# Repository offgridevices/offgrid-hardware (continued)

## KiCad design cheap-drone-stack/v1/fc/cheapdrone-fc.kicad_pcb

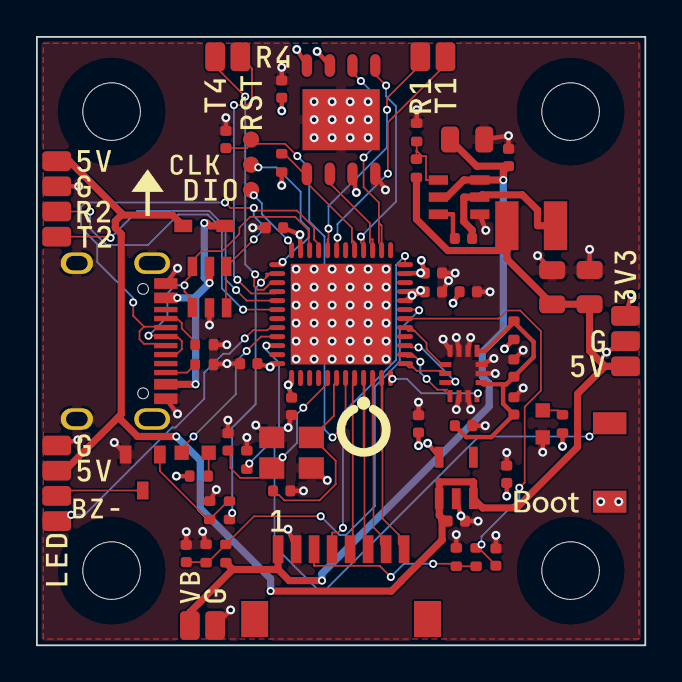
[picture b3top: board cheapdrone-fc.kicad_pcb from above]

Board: 4 copper layers, 33.8 x 33.8 mm, 77 parts (0 on the bottom side), 49 nets.

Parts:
C1, C2, C4, C5, C10, C11, C12, C13, C14, C17, C21, C22, C23: 100nF; C_0402_1005Metric
C3: 10uF; C_0805_2012Metric
C6, C7: 22uF; C_0805_2012Metric
C8, C15: 1uF; C_0402_1005Metric
C9, C16, C20: 4.7uF; C_0402_1005Metric
C18, C19: 12pF; C_0402_1005Metric
D_USB: 1N5819WS; SOD-323_L1.8-W1.3-LS2.5-RD
H1, H2, H3, H4: HOLE; HOLE_M3
J_ESC: SH-8P RA; CONN-TH_SM08B-SRSS-TB-LF-SN
J_USB: USB-C; USB-C_SMD-TYPE-C-31-M-12_1
L1: 4.7uH; IND-SMD_L3.0-W3.0_FNR30XXS
LED_PWR: RED; LED-SMD_L1.6-W0.8-R-RD
LED_STAT: BLUE; LED0603-RD_BLUE
P_3V3, P_5V: PAD_SIG
P_BZ+: PAD_SIG
P_BZ-: PAD_SIG
P_G1, P_G2, P_G3: PAD_SIG
P_LED: PAD_SIG
P_R1, P_R2, P_R4: PAD_SIG
P_RX5V: PAD_SIG
P_RXG: PAD_SIG
P_T1, P_T2, P_T4: PAD_SIG
P_VBAT: PAD_SIG
Q_BZ: 2N7002; SOT-23-3_L2.9-W1.3-P1.90-LS2.4-BR
R1: 100k; R_0402_1005Metric
R2, R4, R12, R13: 1k; R_0402_1005Metric
R3, R7, R9, R15: 10k; R_0402_1005Metric
R5: 15k; R_0402_1005Metric
R6: 2k; R_0402_1005Metric
R8: 10R; R_0402_1005Metric
R10, R11: 5.1k; R_0402_1005Metric
R14: 100R; R_0402_1005Metric
SW_BOOT: BOOT; SW-SMD_L3.9-W3.0-P4.45
TP_NRST: PAD_TP
TP_SWCLK: PAD_TP
TP_SWDIO: PAD_TP
U_BUCK: LMR51420YDDCR; SOT-23-6_L2.9-W1.6-P0.95-LS2.9-BL
U_ESD: USBLC6-2SC6; SOT-23-6_L2.9-W1.6-P0.95-LS2.8-BL
U_FC: STM32G473CEU6; UFQFPN-48_L7.0-W7.0-P0.50-BL-EP5.6
U_FLASH: W25Q128JVPIQ; WSON-8_L6.0-W5.0-P1.27-BL-EP
U_IMU: ICM-42688-P; LGA-14_L3.0-W2.5-P0.50-TL
U_LDO: ME6211C33; SOT-23-5_L3.0-W1.7-P0.95-LS2.8-BL
Y1: 8MHz; CRYSTAL-SMD_4P-L3.2-W2.5-BL

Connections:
+3V3: C9.1, C10.1, C11.1, C12.1, C13.1, C14.1, C15.1, C16.1, C23.1, P_3V3.1, R8.1, R9.1, R12.1, R13.1, SW_BOOT.1, U_FC.1, U_FC.20, U_FC.21, U_FC.23, U_FC.35, U_FC.48, U_FLASH.3, U_FLASH.7, U_FLASH.8, U_LDO.5
+3V3_GYRO: C20.1, C21.1, C22.1, R8.2, U_IMU.5, U_IMU.8
+5V: C6.1, C7.1, C8.1, D_USB.1, L1.2, P_5V.1, P_BZ+.1, P_RX5V.1, R5.1, U_LDO.1, U_LDO.3
ADC_CURR: C1.1, R2.2, U_FC.18
ADC_VBAT: C2.1, R3.2, R4.1, U_FC.19
BEEPER: R14.1, U_FC.38
BEEPER_G: Q_BZ.1, R14.2, R15.1
BOOT0: R7.1, SW_BOOT.2, U_FC.46
BUCK_CB: C5.1, U_BUCK.6
BUCK_FB: R5.2, R6.1, U_BUCK.4
BUCK_SW: C5.2, L1.1, U_BUCK.2
BZ-: P_BZ-.1, Q_BZ.3
CUR: J_ESC.3, R1.1, R2.1
FLASH_CS: R9.2, U_FC.29, U_FLASH.1
GND: C1.2, C2.2, C3.2, C4.2, C6.2, C7.2, C8.2, C9.2, C10.2, C11.2, C12.2, C13.2, C14.2, C15.2, C16.2, C17.2, C18.2, C19.2, C20.2, C21.2, C22.2, C23.2, J_ESC.2, J_USB.1, J_USB.2, J_USB.3, J_USB.4, J_USB.A1B12, J_USB.B1A12, LED_PWR.2, P_G1.1, P_G2.1, P_G3.1, P_RXG.1, Q_BZ.2, R1.2, R4.2, R6.2, R7.2, R10.2, R11.2, R15.2, U_BUCK.1, U_ESD.2, U_FC.49, U_FLASH.4, U_FLASH.9, U_IMU.2, U_IMU.3, U_IMU.6, U_IMU.7, U_IMU.9, U_IMU.10, U_IMU.11, U_LDO.2, Y1.2, Y1.4
GYRO_CS: U_FC.17, U_IMU.12
GYRO_INT: U_FC.12, U_IMU.4
HSE_IN: C18.1, U_FC.5, Y1.1
HSE_OUT: C19.1, U_FC.6, Y1.3
LED0: LED_STAT.1, U_FC.45
LED0_A: LED_STAT.2, R13.2
LED_PWR_A: LED_PWR.1, R12.2
LED_STRIP: P_LED.1, U_FC.44
M1_SIG: J_ESC.5, U_FC.8
M2_SIG: J_ESC.6, U_FC.9
M3_SIG: J_ESC.7, U_FC.10
M4_SIG: J_ESC.8, U_FC.11
NRST: C17.1, TP_NRST.1, U_FC.7
SPI1_MISO: U_FC.14, U_IMU.1
SPI1_MOSI: U_FC.15, U_IMU.14
SPI1_SCK: U_FC.13, U_IMU.13
SPI2_MISO: U_FC.27, U_FLASH.2
SPI2_MOSI: U_FC.28, U_FLASH.5
SPI2_SCK: U_FC.26, U_FLASH.6
SWCLK: TP_SWCLK.1, U_FC.37
SWDIO: TP_SWDIO.1, U_FC.36
TLM: J_ESC.4, U_FC.24
UART1_RX: P_R1.1, U_FC.32
UART1_TX: P_T1.1, U_FC.31
UART2_RX: P_R2.1, U_FC.42
UART2_TX: P_T2.1, U_FC.41
UART4_RX: P_R4.1, U_FC.40
UART4_TX: P_T4.1, U_FC.39
USB_CC1: J_USB.A5, R10.1
USB_CC2: J_USB.B5, R11.1
USB_DM: J_USB.A7, J_USB.B7, U_ESD.3, U_ESD.4, U_FC.33
USB_DP: J_USB.A6, J_USB.B6, U_ESD.1, U_ESD.6, U_FC.34
USB_VBUS: D_USB.2, J_USB.A4B9, J_USB.B4A9, U_ESD.5
VBAT: C3.1, C4.1, J_ESC.1, P_VBAT.1, R3.1, U_BUCK.3, U_BUCK.5

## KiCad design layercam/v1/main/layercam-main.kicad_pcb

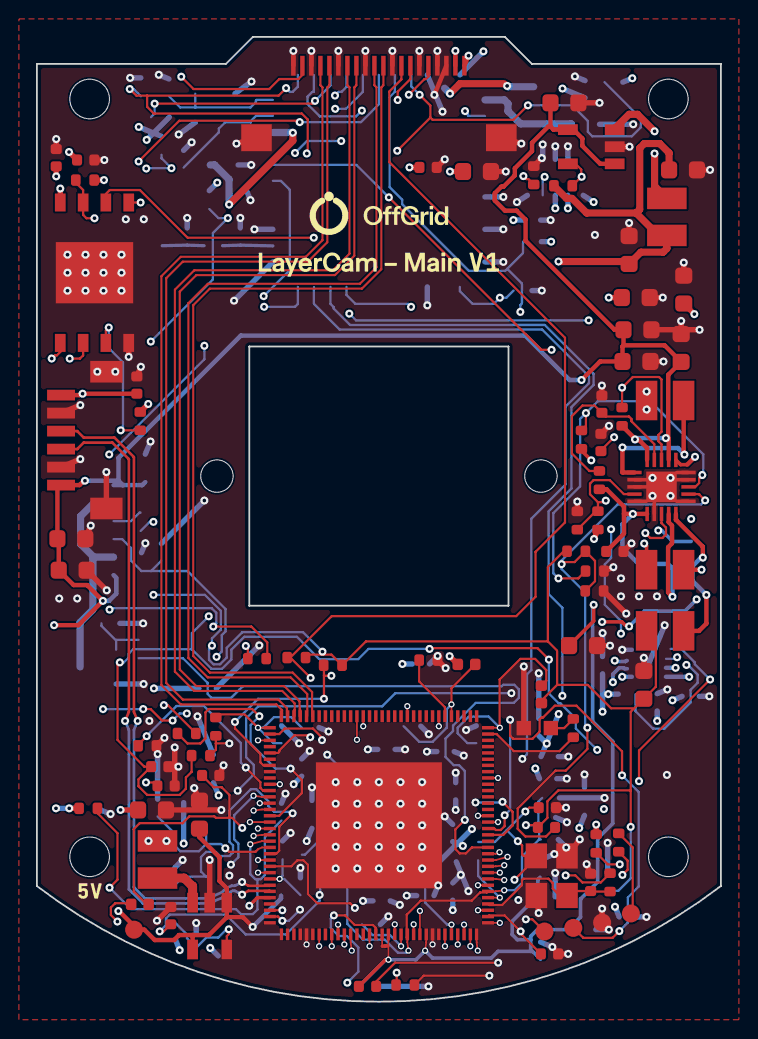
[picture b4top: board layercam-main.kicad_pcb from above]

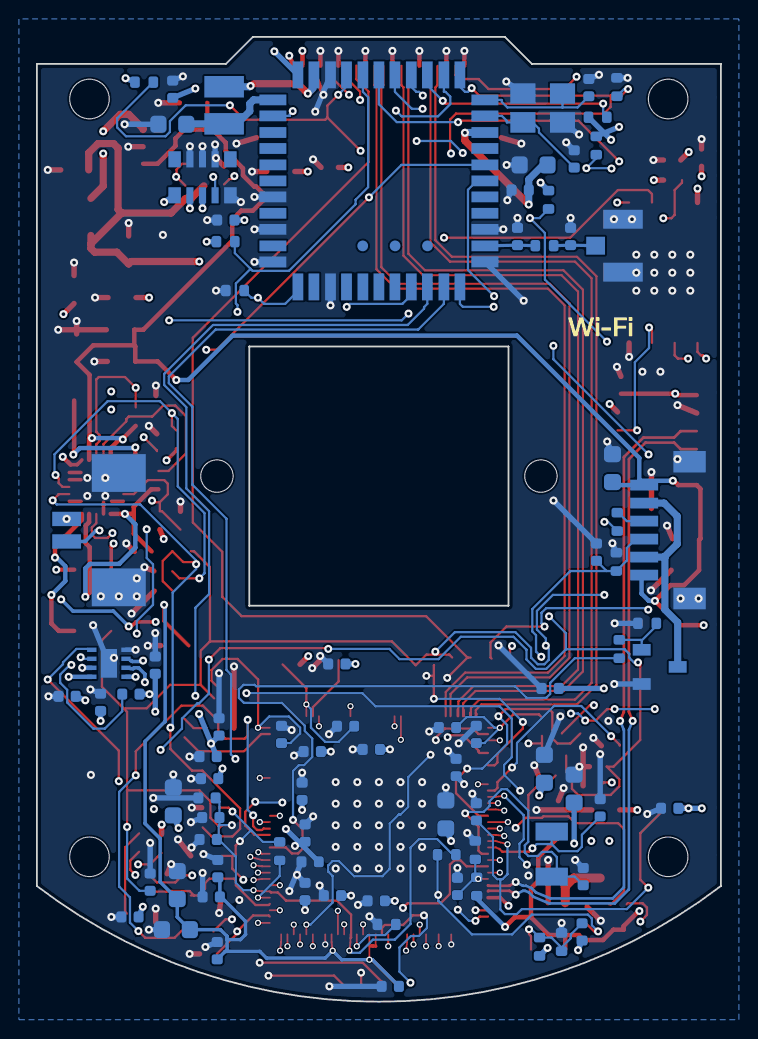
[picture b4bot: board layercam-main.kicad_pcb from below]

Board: 6 copper layers, 38.0 x 53.6 mm, 168 parts (83 on the bottom side), 94 nets.

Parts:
C1, C2, C5, C8, C9, C10, C21, C33, C34, C35, C40, C41, C53, C74, C78, C83: 10uF; C_0603_1608Metric
C3, C4, C24, C25, C26, C27, C28, C29, C36, C37, C38, C42, C43, C44, C46, C47, C48, C49, C50, C51, C52, C54, C56, C59, C60, C68, C71, C72, C77, C79, C81, C82: 100nF; C_0402_1005Metric
C6: 6.8pF; C_0402_1005Metric
C7, C15, C16, C18, C20, C22, C23, C70: 22uF; C_0603_1608Metric
C11, C30, C31, C32, C39, C45, C55, C57, C61, C69, C80: 1uF; C_0402_1005Metric
C12: 330nF; C_0402_1005Metric
C13: 470nF; C_0402_1005Metric
C14, C17, C19: 220pF; C_0402_1005Metric
C58, C73: 4.7uF; C_0402_1005Metric
C62, C63, C64, C65: 18pF; C_0402_1005Metric
C66: 10nF; C_0402_1005Metric
C67: 1nF; C_0402_1005Metric
C75, C76: 12pF; C_0402_1005Metric
C90, C91: DNP_C0402; C_0402_1005Metric
H1, H2, H3, H4: HOLE_M2; MOUNT_M2
H5, H6: HOLE_M1V6; MOUNT_M1V6
J1, J4: SH 6; CONN-SMD-6P-P1.00_BM06B-SRSS-TB-LF-SN
J2: CAM; FPC-SMD_20P-P0.50_XF2M-2015-1A
J3: IR-cut; CONN-SMD_532610271
J5: U.FL; RF-SMD_FRF05002-JSS103M
L1, L5: 2.2uH; IND-SMD_L2.5-W2.0
L2, L3, L4: 1.5uH; IND-SMD_L2.5-W2.0
L6: 4.7uH; IND-SMD_L2.5-W2.0
L7, L8, L9: 120R@100MHz; L_0402_1005Metric
LED1: green; LED0603-RD
Q1: AO3400A; SOT-23-3_L2.9-W1.3-P1.90-LS2.4-BR
R1, R23, R27, R28, R30, R31, R32, R33, R34: 10k; R_0402_1005Metric
R2: 18k; R_0402_1005Metric
R3: 51k; R_0402_1005Metric
R4, R5, R7, R10, R12, R13, R36, R37, R42: 100k; R_0402_1005Metric
R6, R11: 200k; R_0402_1005Metric
R8: 22.6k; R_0402_1005Metric
R9: 127k; R_0402_1005Metric
R14: 20k; R_0402_1005Metric
R15, R16: 1R; R_0402_1005Metric
R17: 6.2k; R_0402_1005Metric
R18: 240R; R_0402_1005Metric
R19, R24, R41: 100R; R_0402_1005Metric
R20, R26, R29, R38: 22R; R_0402_1005Metric
R21: 1M; R_0402_1005Metric
R22, R25, R35, R43: 1k; R_0402_1005Metric
R39, R40: 4.7k; R_0402_1005Metric
R44: 22k; R_0402_1005Metric
R90: 0R; R_0402_1005Metric
TP1, TP2, TP3, TP4, TP5: TP; PAD_TP
U1: RV1106G3; QFN-128_L12.3-W12.3-P0.35-TL-EP7.0-1
U2, U4: TLV62569; SOT-23-5_L3.0-W1.7-P0.95-LS2.8-BR
U3: EA3036C; WQFN-20_L3.0-W3.0-P0.40-BL-EP
U5: W25N02KV; WSON-8_L8.0-W6.0-P1.27-TL-EP-1
U6: AP6256; QFN-44_L12.0-W12.0-P0.90-TL_AP6256
U7: DRV8210P; WSON-8_L2.0-W2.0-P0.50-TL-EP
Y1: 24MHz; CRYSTAL-SMD_4P-L3.2-W2.5-BL
Y2: 32.768kHz; FC-135R_L3.2-W1.5
Y3: 37.4MHz; CRYSTAL-SMD_4P-L3.2-W2.5-BL_1
Y4: 32.768kHz; TG-3541CE

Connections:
ALS: C82.1, J4.4, R44.1, U1.22
ALS_VCC: J4.3, R43.2
ANT: C91.1, J5.1, R90.2
ANT_FEED: C90.1, R90.1, U6.2
BOOT_KEY: C67.1, R23.1, R24.1, U1.23
BOOT_SW: R24.2, TP5.1
BT_CTS: U1.65, U6.41
BT_HOST_WAKE: U1.63, U6.7
BT_REG_ON: R37.1, U1.59, U6.34
BT_RTS: U1.64, U6.44
BT_RXD: U1.76, U6.42
BT_TXD: U1.75, U6.43
BT_WAKE: U1.60, U6.6
CAM_MCLK: J2.2, R38.2
CAM_MCLK_SOC: R38.1, U1.2
CAM_RST: J2.16, U1.3
CAM_SCL: J2.13, R39.1, U1.5
CAM_SDA: J2.14, R40.1, U1.7
CODEC_VCM: C58.1, U1.30
CSI_CKN: J2.8, U1.125
CSI_CKP: J2.7, U1.126
CSI_D0N: J2.5, U1.127
CSI_D0P: J2.4, U1.128
CSI_D1N: J2.11, U1.123
CSI_D1P: J2.10, U1.124
DBG_RX: TP2.1, U1.80
DBG_TX: TP1.1, U1.79
DRAM_ZQ: R18.1, U1.52
EN_3V3: C13.1, R6.2, U3.9
EN_MID: C12.1, R5.2, U3.8, U3.18
ETH_EXTR: R17.1, U1.102
FB_0V9: C6.2, R3.2, R4.1, U2.5
FB_1V8: C19.2, R11.2, R12.1, U3.2
FB_3V3: C14.2, R7.2, R8.1, U3.14
FB_DDR: C17.2, R9.2, R10.1, U3.3
FB_WIFI: R13.2, R14.1, U4.5
GND: C1.2, C2.2, C3.2, C4.2, C5.2, C7.2, C8.2, C9.2, C10.2, C11.2, C12.2, C13.2, C15.2, C16.2, C18.2, C20.2, C21.2, C22.2, C23.2, C24.2, C25.2, C26.2, C27.2, C28.2, C29.2, C30.2, C31.2, C32.2, C33.2, C34.2, C35.2, C36.2, C37.2, C38.2, C39.2, C40.2, C41.2, C42.2, C43.2, C44.2, C45.2, C46.2, C47.2, C48.2, C49.2, C50.2, C51.2, C52.2, C53.2, C54.2, C55.2, C56.2, C57.2, C58.2, C59.2, C60.2, C61.2, C62.2, C63.2, C64.2, C65.2, C66.2, C67.2, C68.2, C69.2, C70.2, C71.2, C72.2, C73.2, C74.2, C75.2, C76.2, C77.2, C78.2, C79.2, C80.2, C81.2, C82.2, C83.2, C90.2, C91.2, J1.2, J1.5, J1.7, J1.8, J2.1, J2.3, J2.6, J2.9, J2.12, J2.15, J2.17, J2.18, J2.21, J2.22, J3.3, J3.4, J4.7, J4.8, J5.2, J5.3, LED1.1, Q1.2, R2.2, R4.2, R8.2, R10.2, R12.2, R14.2, R17.2, R18.2, R35.2, R36.2, R37.2, R42.2, R44.2, TP3.1, U1.37, U1.57, U1.129, U2.2, U3.1, U3.4, U3.5, U3.12, U3.13, U3.15, U3.17, U3.21, U4.2, U5.4, U5.9, U6.1, U6.3, U6.20, U6.29, U6.31, U6.33, U6.36, U7.4, U7.9, Y1.2, Y1.4, Y3.2, Y3.4, Y4.5, Y4.7, Y4.8, Y4.9
IRCUT_1: J3.1, U7.2
IRCUT_2: J3.2, U7.3
IRCUT_A: U1.72, U7.6
IRCUT_B: U1.73, U7.5
IR_GATE: Q1.1, R41.2, R42.1
IR_PWM: R41.1, U1.77
LED_K: J4.2, J4.5, Q1.3
LED_STATUS: R25.1, U1.95
LED_STATUS_A: LED1.2, R25.2
LX_1V8: L4.1, U3.20
LX_3V3: L2.1, U3.11
LX_DDR: L3.1, U3.6
NAND_CLK: R26.2, U5.6
NAND_CLK_SOC: R26.1, U1.48
NAND_CS: U1.47, U5.1
NAND_IO0: U1.41, U5.5
NAND_IO1: U1.42, U5.2
NAND_IO2: R27.1, U1.44, U5.3
NAND_IO3: R28.1, U1.39, U5.7
NPOR: C66.1, R22.1, U1.66
RTC_XIN: C64.1, U1.21, Y2.1
RTC_XOUT: C65.1, U1.20, Y2.2
SD_CLK: R29.2, U6.17
SD_CLK_SOC: R29.1, U1.15
SD_CMD: R30.1, U1.16, U6.16
SD_D0: R31.1, U1.14, U6.18
SD_D1: R32.1, U1.12, U6.19
SD_D2: R33.1, U1.18, U6.14
SD_D3: R34.1, U1.17, U6.15
SD_DET: R35.1, U1.11
SW_0V9: L1.1, U2.3
SW_WIFI: L5.1, U4.3
USB_DM: J1.3, U1.26
USB_DP: J1.4, U1.27
USB_VBUSDET: C4.1, R1.2, R2.1, U1.25
VCC_1V8: C19.1, C20.1, C42.1, C43.1, C44.1, C45.1, L4.2, L7.1, L8.1, R11.1, R15.1, R16.1, R23.2, R39.2, R40.2, R43.1, U1.53, U1.70
VCC_1V8_ADC: C56.1, R16.2, U1.24
VCC_1V8_CODEC: C57.1, L7.2, U1.31
VCC_1V8_MIPI: C54.1, C55.1, R15.2, U1.1
VCC_1V8_OTP: C59.1, L8.2, U1.96
VCC_3V3: C14.1, C15.1, C16.1, C46.1, C47.1, C48.1, C49.1, C50.1, C51.1, C52.1, C53.1, C68.1, C69.1, C72.1, C73.1, C77.1, C78.1, C79.1, C80.1, C81.1, J2.19, J2.20, L2.2, L9.1, R7.1, R19.1, R22.2, R27.2, R28.2, R30.2, R31.2, R32.2, R33.2, R34.2, U1.13, U1.28, U1.43, U1.61, U1.81, U1.88, U1.108, U5.8, U6.22, U7.1, U7.7, U7.8, Y4.1, Y4.2, Y4.3
VCC_3V3_ETH: C60.1, L9.2, U1.101
VCC_DDR: C17.1, C18.1, C36.1, C37.1, C38.1, C39.1, C40.1, C41.1, L3.2, R9.1, U1.49, U1.50, U1.56
VCC_RTC: C61.1, R19.2, U1.19
VDD_0V9: C6.1, C7.1, C24.1, C25.1, C26.1, C27.1, C28.1, C29.1, C30.1, C31.1, C32.1, C33.1, C34.1, C35.1, L1.2, R3.1, U1.10, U1.51, U1.54, U1.55, U1.67, U1.71, U1.82, U1.103, U1.115, U1.116
VSYS: C1.1, C2.1, C3.1, C5.1, C8.1, C9.1, C10.1, C11.1, C21.1, C83.1, J1.1, J1.6, J4.1, J4.6, R1.1, R5.1, R6.1, TP4.1, U2.1, U2.4, U3.7, U3.10, U3.16, U3.19, U4.1, U4.4
VWIFI: C22.1, C23.1, C70.1, C71.1, L5.2, R13.1, U6.9
WIFI_LPO: U6.24, Y4.4
WIFI_LX: L6.1, U6.21
WIFI_VLDO: C74.1, L6.2, U6.23
WL_HOST_WAKE: U1.62, U6.13
WL_REG_ON: R36.1, U1.74, U6.12
XIN_24M: C62.1, R21.1, U1.68, Y1.1
XOUT_24M: R20.1, U1.69
XOUT_24M_X: C63.1, R20.2, R21.2, Y1.3
XTAL37_IN: C75.1, U6.10, Y3.1
XTAL37_OUT: C76.1, U6.11, Y3.3

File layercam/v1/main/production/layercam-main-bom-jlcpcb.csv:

Comment,Designator,Footprint,LCSC Part #
1k,"R22,R25,R35,R43",R_0402_1005Metric,C11702
green,LED1,LED0603-RD,C12624
TLV62569,"U2,U4",SOT-23-5_L3.0-W1.7-P0.95-LS2.8-BR,C141836
10nF,C66,C_0402_1005Metric,C15195
1nF,C67,C_0402_1005Metric,C1523
100nF,"C3,C4,C24,C25,C26,C27,C28,C29,C36,C37,C38,C42,C43,C44,C46,C47,C48,C49,C50,C51,C52,C54,C56,C59,C60,C68,C71,C72,C77,C79,C81,C82",C_0402_1005Metric,C1525
12pF,"C75,C76",C_0402_1005Metric,C1547
18pF,"C62,C63,C64,C65",C_0402_1005Metric,C1549
6.8pF,C6,C_0402_1005Metric,C1576
SH 6,"J1,J4",CONN-SMD-6P-P1.00_BM06B-SRSS-TB-LF-SN,C160392
0R,R90,R_0402_1005Metric,C17168
IR-cut,J3,CONN-SMD_532610271,C177225
330nF,C12,C_0402_1005Metric,C18164591
32.768kHz,Y2,FC-135R_L3.2-W1.5,C1985607
32.768kHz,Y4,TG-3541CE,C1987384
AO3400A,Q1,SOT-23-3_L2.9-W1.3-P1.90-LS2.4-BR,C20917
100R,"R19,R24,R41",R_0402_1005Metric,C25076
1R,"R15,R16",R_0402_1005Metric,C25086
22R,"R20,R26,R29,R38",R_0402_1005Metric,C25092
240R,R18,R_0402_1005Metric,C25094
100k,"R4,R5,R7,R10,R12,R13,R36,R37,R42",R_0402_1005Metric,C25741
10k,"R1,R23,R27,R28,R30,R31,R32,R33,R34",R_0402_1005Metric,C25744
127k,R9,R_0402_1005Metric,C25751
18k,R2,R_0402_1005Metric,C25762
200k,"R6,R11",R_0402_1005Metric,C25764
20k,R14,R_0402_1005Metric,C25765
22k,R44,R_0402_1005Metric,C25768
51k,R3,R_0402_1005Metric,C25794
4.7k,"R39,R40",R_0402_1005Metric,C25900
6.2k,R17,R_0402_1005Metric,C25915
1M,R21,R_0402_1005Metric,C26083
22.6k,R8,R_0402_1005Metric,C26960
37.4MHz,Y3,CRYSTAL-SMD_4P-L3.2-W2.5-BL_1,C2981708
W25N02KV,U5,WSON-8_L8.0-W6.0-P1.27-TL-EP-1,C3010298
220pF,"C14,C17,C19",C_0402_1005Metric,C39122
22uF,"C7,C15,C16,C18,C20,C22,C23,C70",C_0603_1608Metric,C393031
24MHz,Y1,CRYSTAL-SMD_4P-L3.2-W2.5-BL,C435181
1uF,"C11,C30,C31,C32,C39,C45,C55,C57,C61,C69,C80",C_0402_1005Metric,C437522
4.7uF,"C58,C73",C_0402_1005Metric,C464981
DRV8210P,U7,WSON-8_L2.0-W2.0-P0.50-TL-EP,C5218852
AP6256,U6,QFN-44_L12.0-W12.0-P0.90-TL_AP6256,C5248079
RV1106G3,U1,QFN-128_L12.3-W12.3-P0.35-TL-EP7.0-1,C5328706
470nF,C13,C_0402_1005Metric,C5448817
EA3036C,U3,WQFN-20_L3.0-W3.0-P0.40-BL-EP,C570857
CAM,J2,FPC-SMD_20P-P0.50_XF2M-2015-1A,C57541
2.2uH,"L1,L5",IND-SMD_L2.5-W2.0,C576403
10uF,"C1,C2,C5,C8,C9,C10,C21,C33,C34,C35,C40,C41,C53,C74,C78,C83",C_0603_1608Metric,C576470
4.7uH,L6,IND-SMD_L2.5-W2.0,C668313
120R@100MHz,"L7,L8,L9",L_0402_1005Metric,C76891
U.FL,J5,RF-SMD_FRF05002-JSS103M,C88374
1.5uH,"L2,L3,L4",IND-SMD_L2.5-W2.0,C909806

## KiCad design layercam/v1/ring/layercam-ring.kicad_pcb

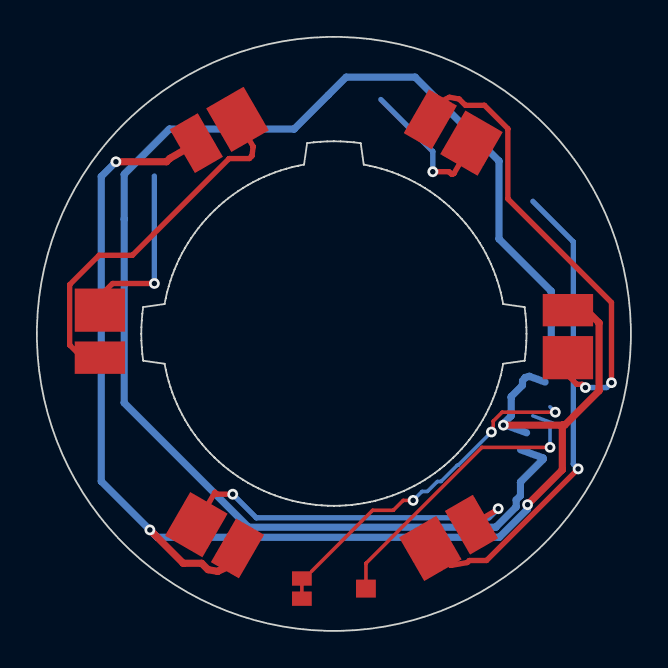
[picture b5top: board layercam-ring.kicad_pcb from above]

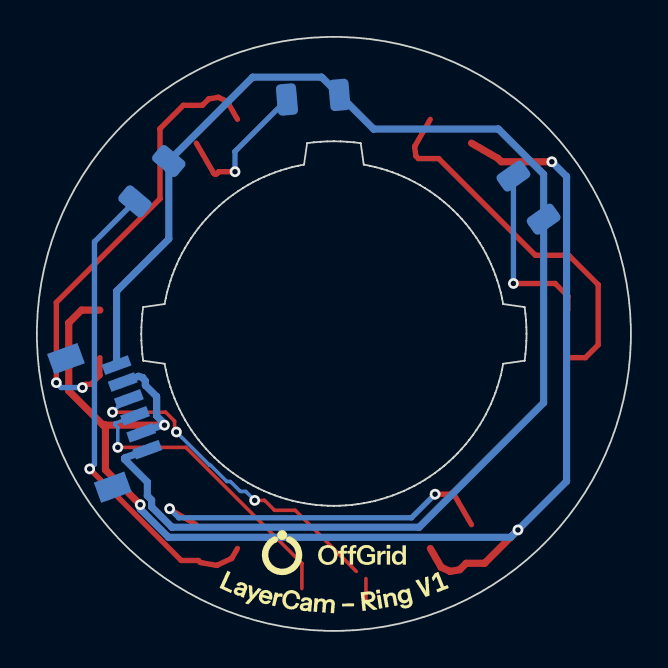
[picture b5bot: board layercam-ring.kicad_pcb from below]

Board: 2 copper layers, 33.0 x 33.0 mm, 11 parts (4 on the bottom side), 10 nets.

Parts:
D1, D2, D3, D4, D5, D6: 850nm; LED-SMD_L3.5-W2.8-R-RD_RED-1
J1: SH 6; CONN-SMD-6P-P1.00_BM06B-SRSS-TB-LF-SN
Q1: TEMT6000; SENSORS-SMD_TEMT6000X01
R1, R2, R3: 47R; R_1206_3216Metric

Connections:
ALS: J1.4, Q1.1, Q1.2
ALS_VCC: J1.3, Q1.3
LED_K: D2.2, D4.2, D6.2, J1.2, J1.5
STR1_A: D1.1, R1.2
STR1_M: D1.2, D2.1
STR2_A: D3.1, R2.2
STR2_M: D3.2, D4.1
STR3_A: D5.1, R3.2
STR3_M: D5.2, D6.1
VSYS: J1.1, J1.6, R1.1, R2.1, R3.1

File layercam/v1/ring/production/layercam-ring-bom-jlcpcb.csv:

Comment,Designator,Footprint,LCSC Part #
SH 6,J1,CONN-SMD-6P-P1.00_BM06B-SRSS-TB-LF-SN,C160392
47R,"R1,R2,R3",R_1206_3216Metric,C17969
850nm,"D1,D2,D3,D4,D5,D6",LED-SMD_L3.5-W2.8-R-RD_RED-1,C7500094
TEMT6000,Q1,SENSORS-SMD_TEMT6000X01,C94098

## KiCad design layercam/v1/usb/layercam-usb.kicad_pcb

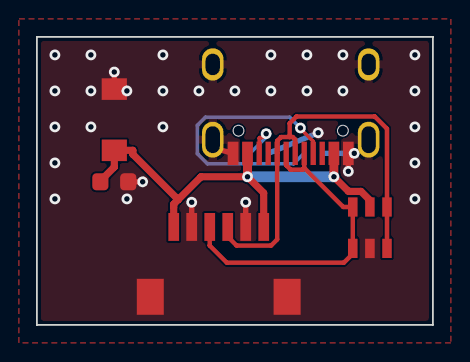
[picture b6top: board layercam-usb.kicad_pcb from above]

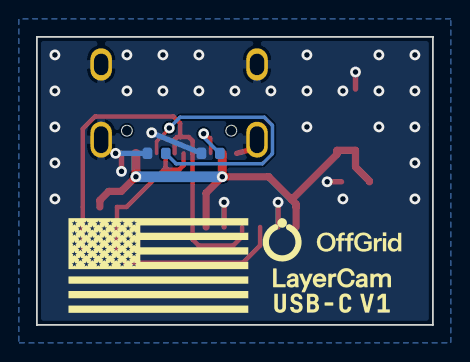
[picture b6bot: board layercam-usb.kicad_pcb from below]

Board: 2 copper layers, 22.0 x 16.0 mm, 7 parts (2 on the bottom side), 6 nets.

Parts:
C1: 10uF; C_0603_1608Metric
D1: SMF6.0CA; SOD-123FL_L2.8-W1.8-LS3.7-BI
J1: USB-C; USB-C_SMD-TYPE-C-31-M-12_1
J2: SH 6; CONN-SMD_SM06B-SRSS-TB-LF-SN
R1, R2: 5.1k; R_0402_1005Metric
U1: USBLC6-2SC6; SOT-23-6_L2.9-W1.6-P0.95-LS2.8-BL

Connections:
CC1: J1.A5, R1.1
CC2: J1.B5, R2.1
GND: C1.2, D1.2, J1.1, J1.2, J1.3, J1.4, J1.A1B12, J1.B1A12, J2.2, J2.5, J2.7, J2.8, R1.2, R2.2, U1.2
USB_DM: J1.A7, J1.B7, J2.3, U1.1, U1.6
USB_DP: J1.A6, J1.B6, J2.4, U1.3, U1.4
VSYS: C1.1, D1.1, J1.A4B9, J1.B4A9, J2.1, J2.6, U1.5

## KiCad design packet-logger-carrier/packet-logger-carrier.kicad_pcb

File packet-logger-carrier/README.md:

# Packet Logger Carrier

Carrier board for the LoRa mesh packet logger: RAK19003 + XIAO ESP32-C6 +
microSD.

| Revision | Status | Folder |
|---|---|---|
| **v1** | Ordered, not yet bench-verified | [`v1/`](v1/) |

v1 predates the per-revision test record (`TESTS.md`); its checks are in
its README. How revisions work across this repository:
[`docs/versioning.md`](../docs/versioning.md).

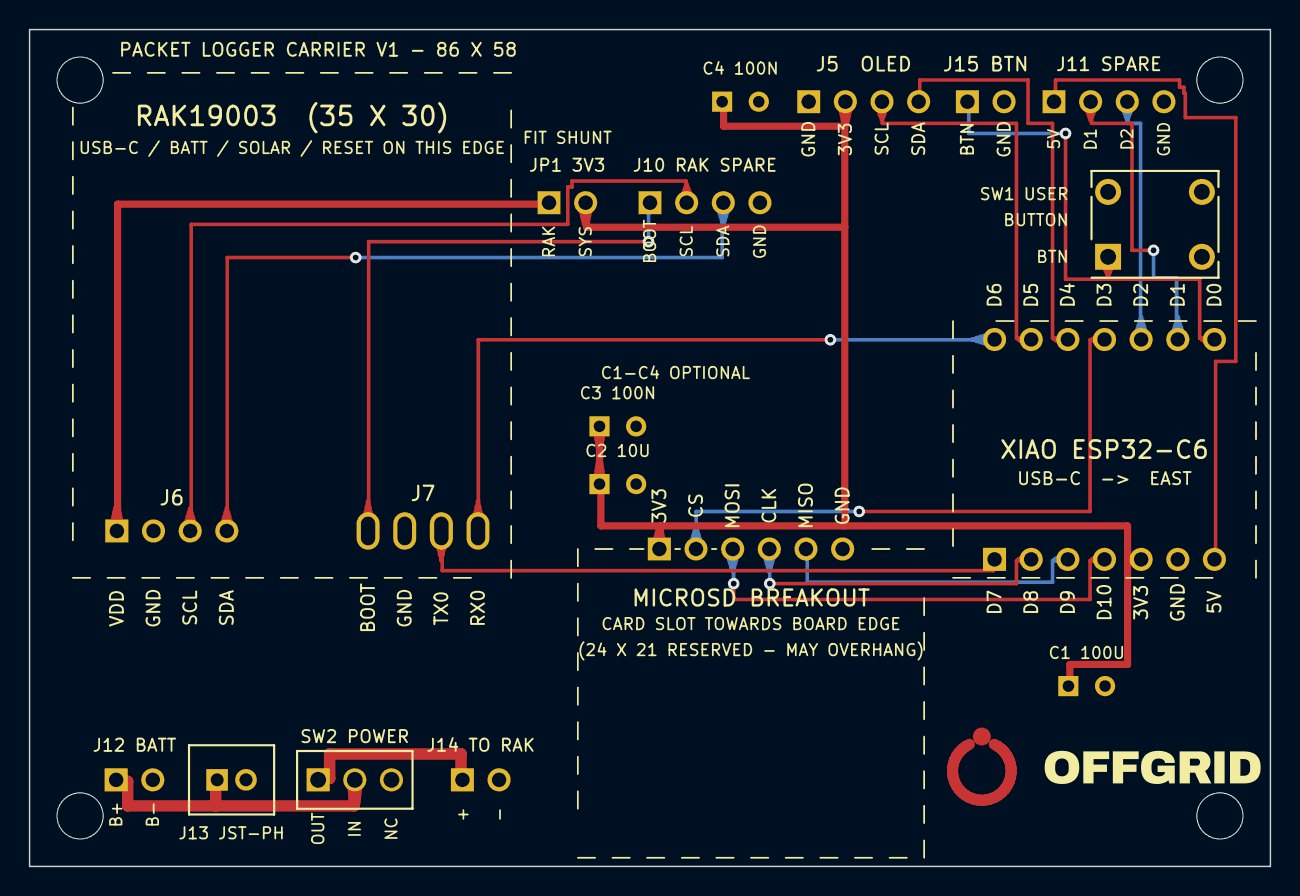
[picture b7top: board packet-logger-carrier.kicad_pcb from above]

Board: 2 copper layers, 86.0 x 58.0 mm, 22 parts (0 on the bottom side), 20 nets.

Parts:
C1: 100u; C1
C2: 10u; C2
C3: 100n; C3
C4: 100n; C4
H1, H2, H3, H4: M3; MountingHole
J1: RAK19003 J6; J1
J2: RAK19003 J7; J2
J3: XIAO ESP32-C6; J3
J4: microSD; J4
J5: LID CABLE; J5
J10: RAK SPARE; J10
J11: ESP SPARE; J11
J12: BATT IN; J12
J13: BATT JST-PH; J13
J14: BATT TO RAK; J14
J15: J15
JP1: 3V3 LINK; JP1
SW1: USER BUTTON; SW1
SW2: POWER SWITCH; SW2

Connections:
+3V3: C1.1, C2.1, C3.1, C4.1, J3.5, J4.1, J5.2, JP1.2
BAT+: J12.1, J13.1, SW2.2
BAT_SW: J14.1, SW2.1
BTN: J3.14, J15.1, SW1.1
GND: C1.2, C2.2, C3.2, C4.2, J1.2, J2.2, J3.6, J4.6, J5.1, J10.4, J11.4, J12.2, J13.2, J14.2, J15.2, SW1.2
OLED_SCL: J3.9, J5.3
OLED_SDA: J3.10, J5.4
RAK_BOOT: J2.1, J10.1
RAK_RX0: J2.4, J3.8
RAK_SCL: J1.3, J10.2
RAK_SDA: J1.4, J10.3
RAK_TX0: J2.3, J3.1
RAW_3V3: J1.1, JP1.1
SD_CLK: J3.2, J4.4
SD_CS: J3.11, J4.2
SD_MISO: J3.3, J4.5
SD_MOSI: J3.4, J4.3
XIAO_5V: J3.7, J11.1
XIAO_D1: J3.13, J11.2
XIAO_D2: J3.12, J11.3
